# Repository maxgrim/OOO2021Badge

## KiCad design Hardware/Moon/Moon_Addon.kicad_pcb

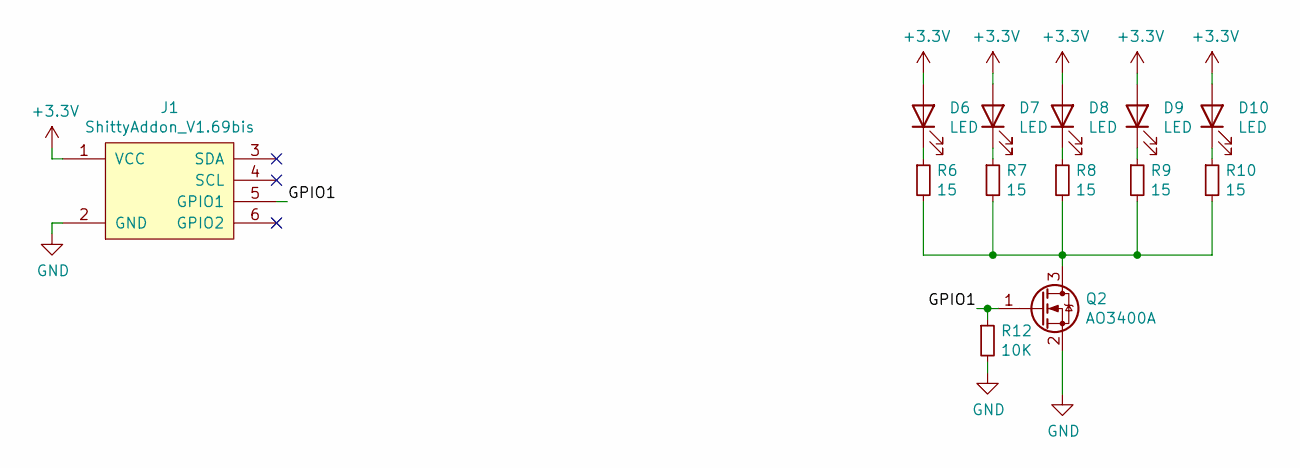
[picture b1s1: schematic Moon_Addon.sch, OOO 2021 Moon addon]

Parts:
D6, D7, D8, D9, D10: LED; LED_0805_2012Metric_Castellated; LCSC C34499
J1: ShittyAddon_V1.69bis; PinHeader_2x03_P2.54mm_Vertical
Q2: AO3400A; SOT-23; LCSC C20917
R6, R7, R8, R9, R10: 15; R_0805_2012Metric_Pad1.20x1.40mm_HandSolder; LCSC C17480
R12: 10K; R_0805_2012Metric_Pad1.20x1.40mm_HandSolder; LCSC C17414

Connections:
+3V3: D6.2 (A), D7.2 (A), D8.2 (A), D9.2 (A), D10.2 (A), J1.1 (VCC)
/GPIO1: J1.5 (GPIO1), Q2.1 (G), R12.1
GND: J1.2 (GND), Q2.2 (S), R12.2
unnamed: D6.1 (K), R6.1
unnamed: D7.1 (K), R7.1
unnamed: D8.1 (K), R8.1
unnamed: D9.1 (K), R9.1
unnamed: D10.1 (K), R10.1
unnamed: Q2.3 (D), R6.2, R7.2, R8.2, R9.2, R10.2

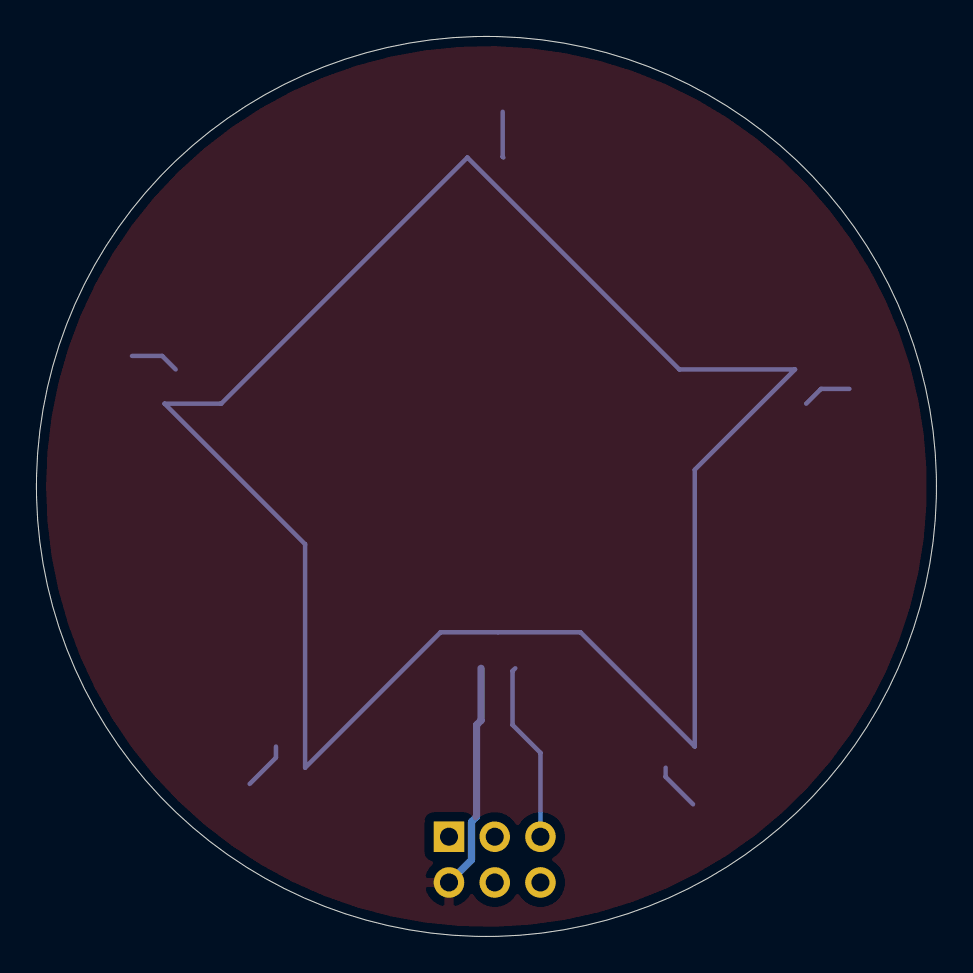
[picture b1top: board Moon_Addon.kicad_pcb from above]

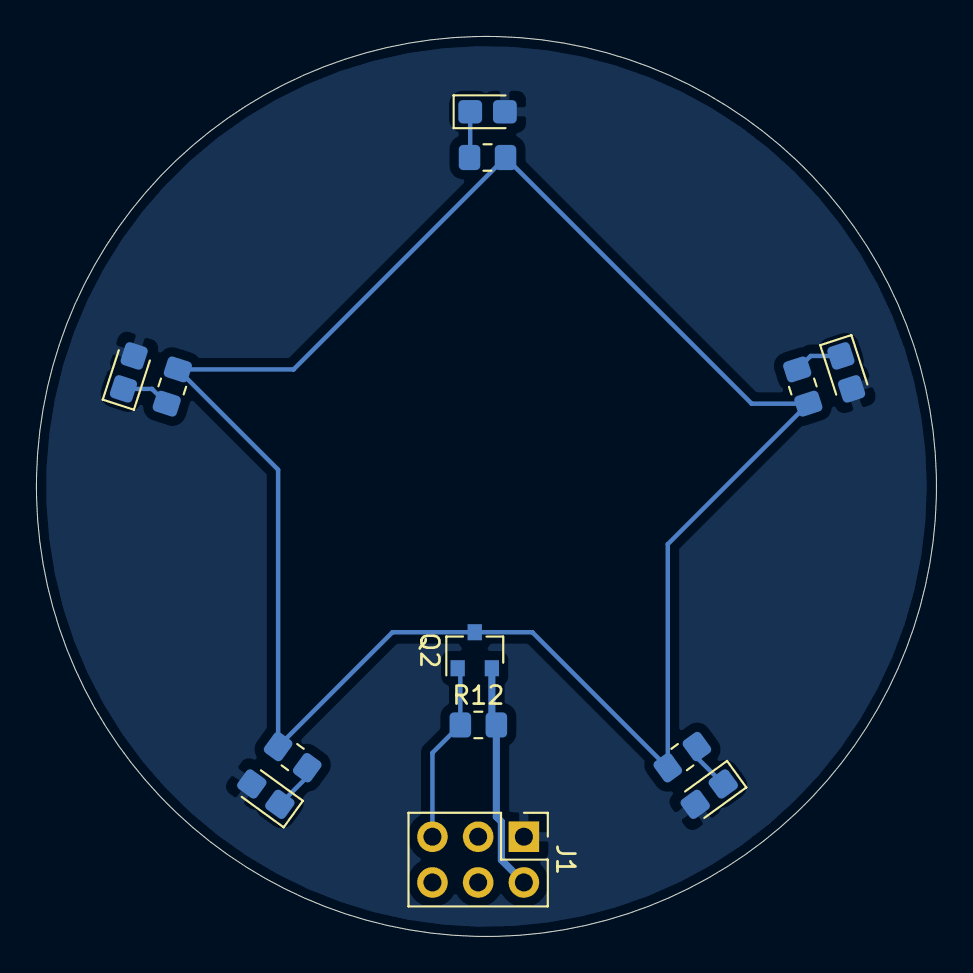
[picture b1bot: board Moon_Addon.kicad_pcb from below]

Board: 2 copper layers, 50.0 x 50.0 mm, 13 parts (13 on the bottom side), 9 nets.

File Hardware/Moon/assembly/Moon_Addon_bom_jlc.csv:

"Comment","Designator","Footprint","LCSC Part #"
"LED","D6,D7,D8,D9,D10","LED_0805_2012Metric_Castellated","C34499"
"AO3400A","Q2","SOT-23","C20917"
"15","R6,R7,R8,R9,R10","R_0805_2012Metric_Pad1.20x1.40mm_HandSolder","C17480"
"10K","R12","R_0805_2012Metric_Pad1.20x1.40mm_HandSolder","C17414"

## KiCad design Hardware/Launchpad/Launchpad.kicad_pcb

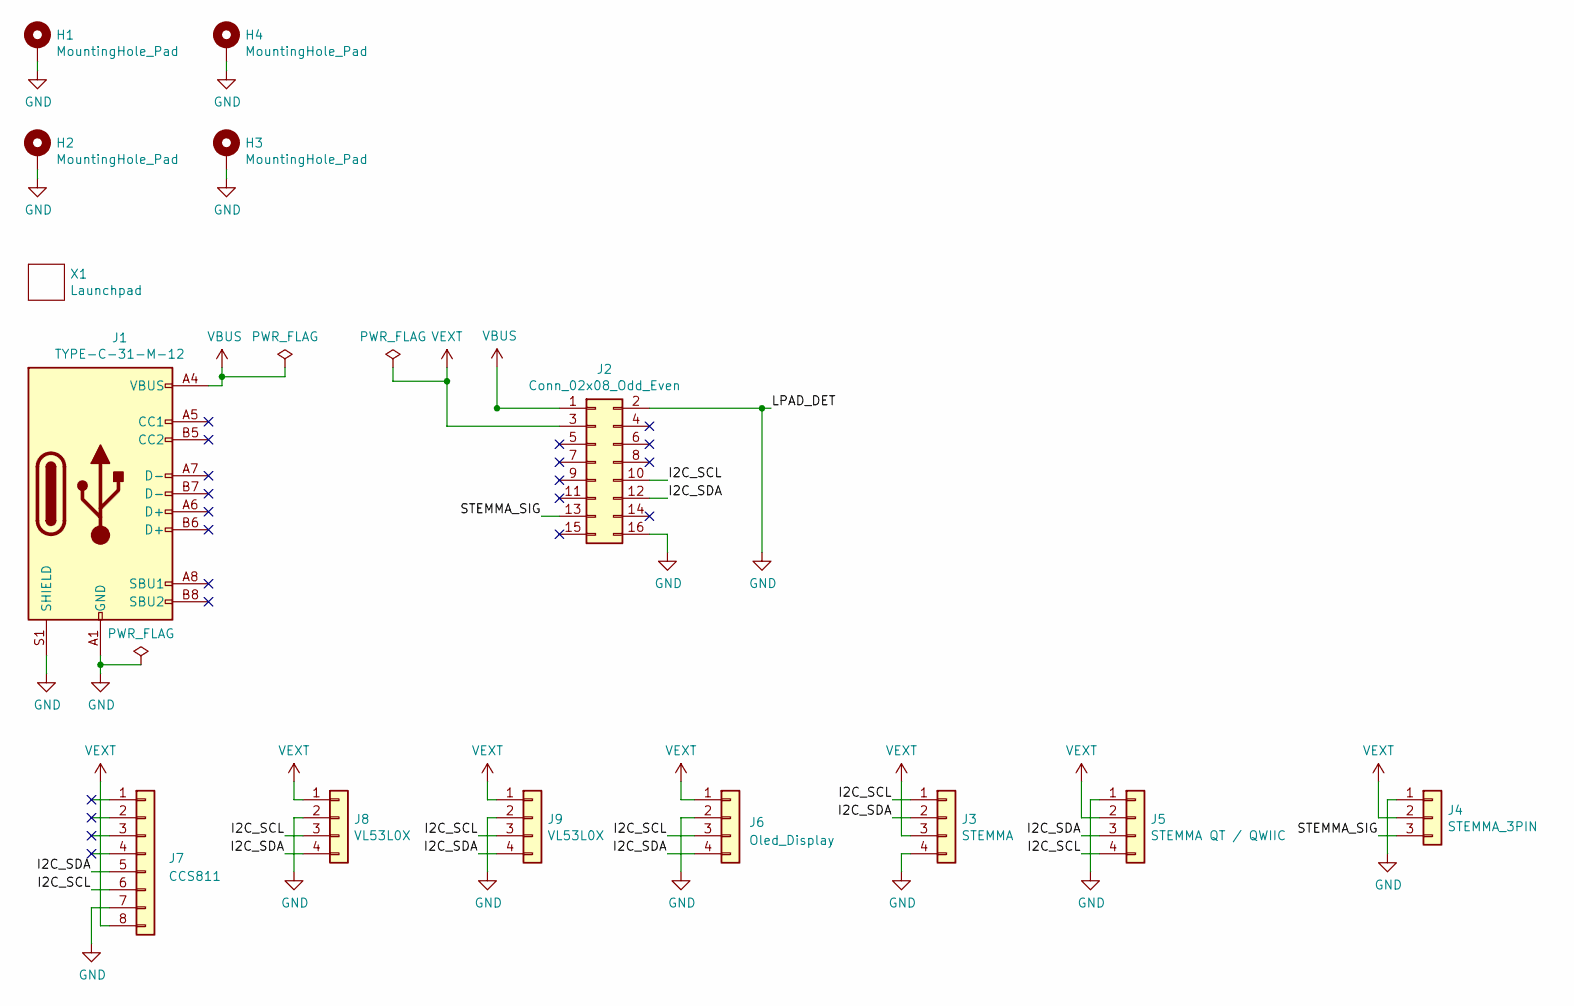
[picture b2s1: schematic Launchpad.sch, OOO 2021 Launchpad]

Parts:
H1, H2, H3, H4: MountingHole_Pad; MountingHole_4.3mm_M4_Pad_Via
J1: TYPE-C-31-M-12; LCSC C165948
J2: Conn_02x08_Odd_Even; PinHeader_2x08_P2.54mm_Horizontal; LCSC C492436
J3: STEMMA; CONN-SMD_2001SMT-4P-WT; LCSC C132498
J4: STEMMA_3PIN; CONN-SMD_3P-P2.00_2001SMT-3P_P; LCSC C155895
J5: STEMMA QT / QWIIC; CONN-SMD_1.0T-4P; LCSC C145956
J6: Oled_Display; PinSocket_1x04_P2.54mm_Horizontal; LCSC C225512
J7: CCS811; PinSocket_1x08_P2.54mm_Vertical; LCSC C350308
J8, J9: VL53L0X; PinSocket_1x04_P2.54mm_Vertical; LCSC C350310
X1: Launchpad

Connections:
/I2C_SCL: J2.10, J3.1, J5.4, J6.3, J7.6, J8.3, J9.3
/I2C_SDA: J2.12, J3.2, J5.3, J6.4, J7.5, J8.4, J9.4
/STEMMA_SIG: J2.13, J4.3
GND: H1.1, H2.1, H3.1, H4.1, J1.A1 (GND), J1.A12 (GND), J1.B1 (GND), J1.B12 (GND), J1.S1 (SHIELD), J2.2, J2.16, J3.4, J4.1, J5.1, J6.2, J7.7, J8.2, J9.2
VBUS: J1.A4 (VBUS), J1.A9 (VBUS), J1.B4 (VBUS), J1.B9 (VBUS), J2.1
VEXT: J2.3, J3.3, J4.2, J5.2, J6.1, J7.8, J8.1, J9.1

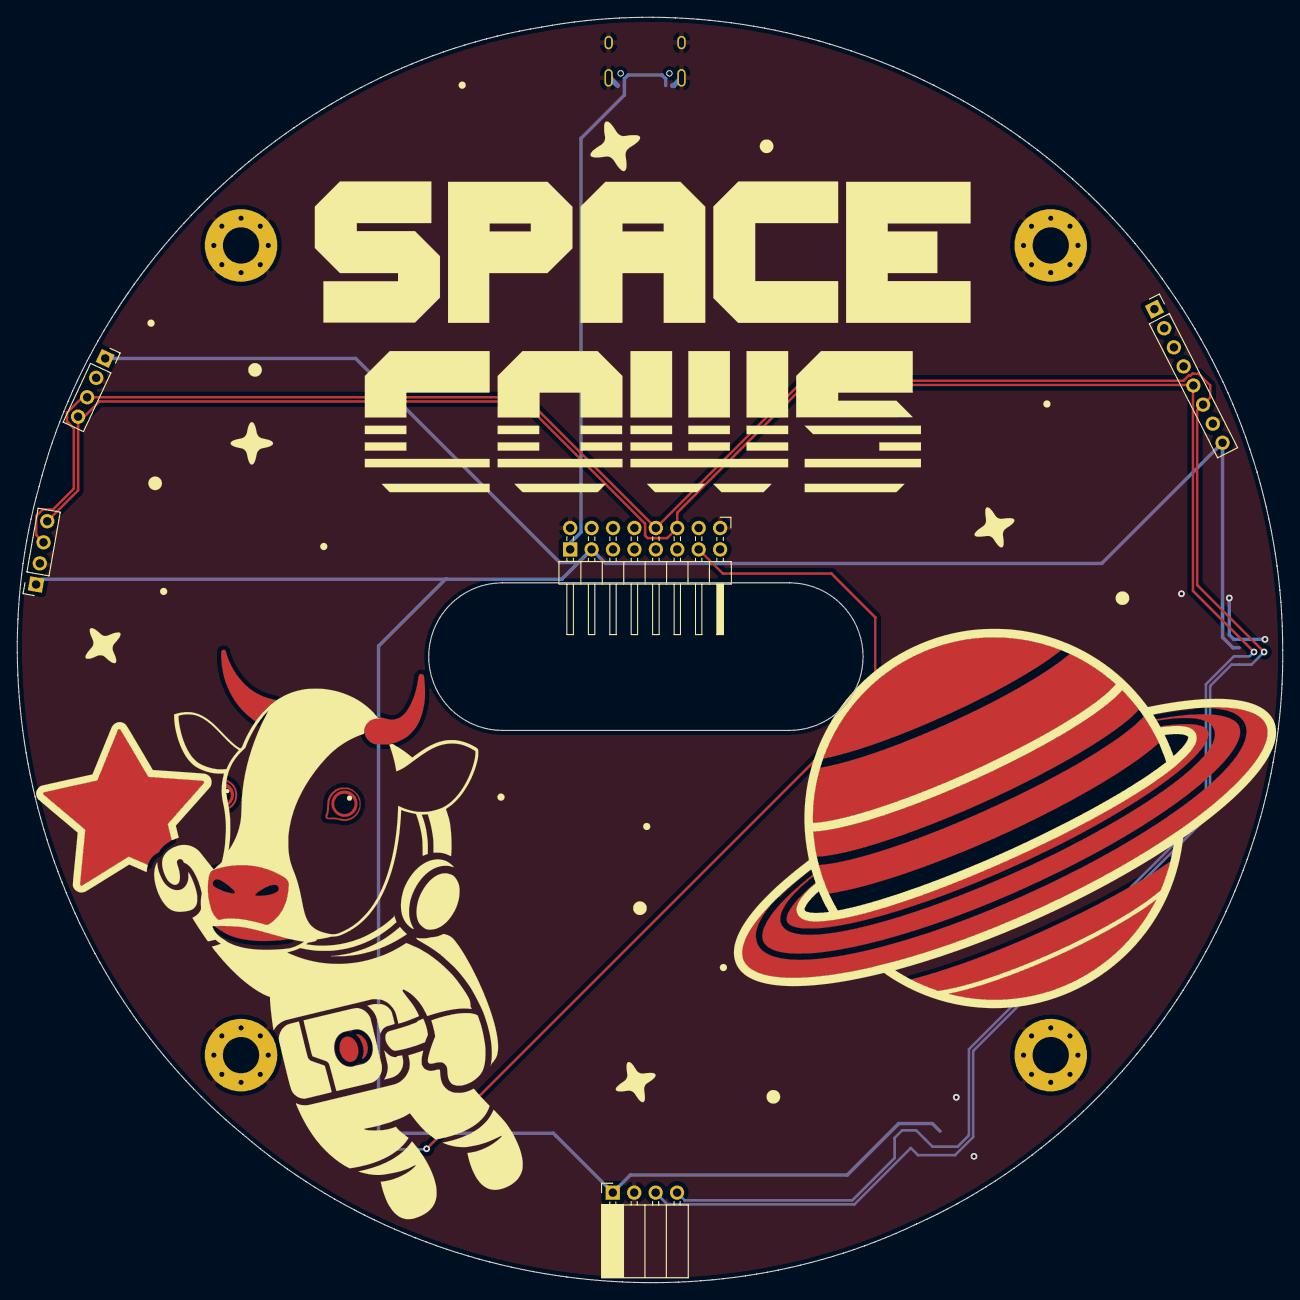
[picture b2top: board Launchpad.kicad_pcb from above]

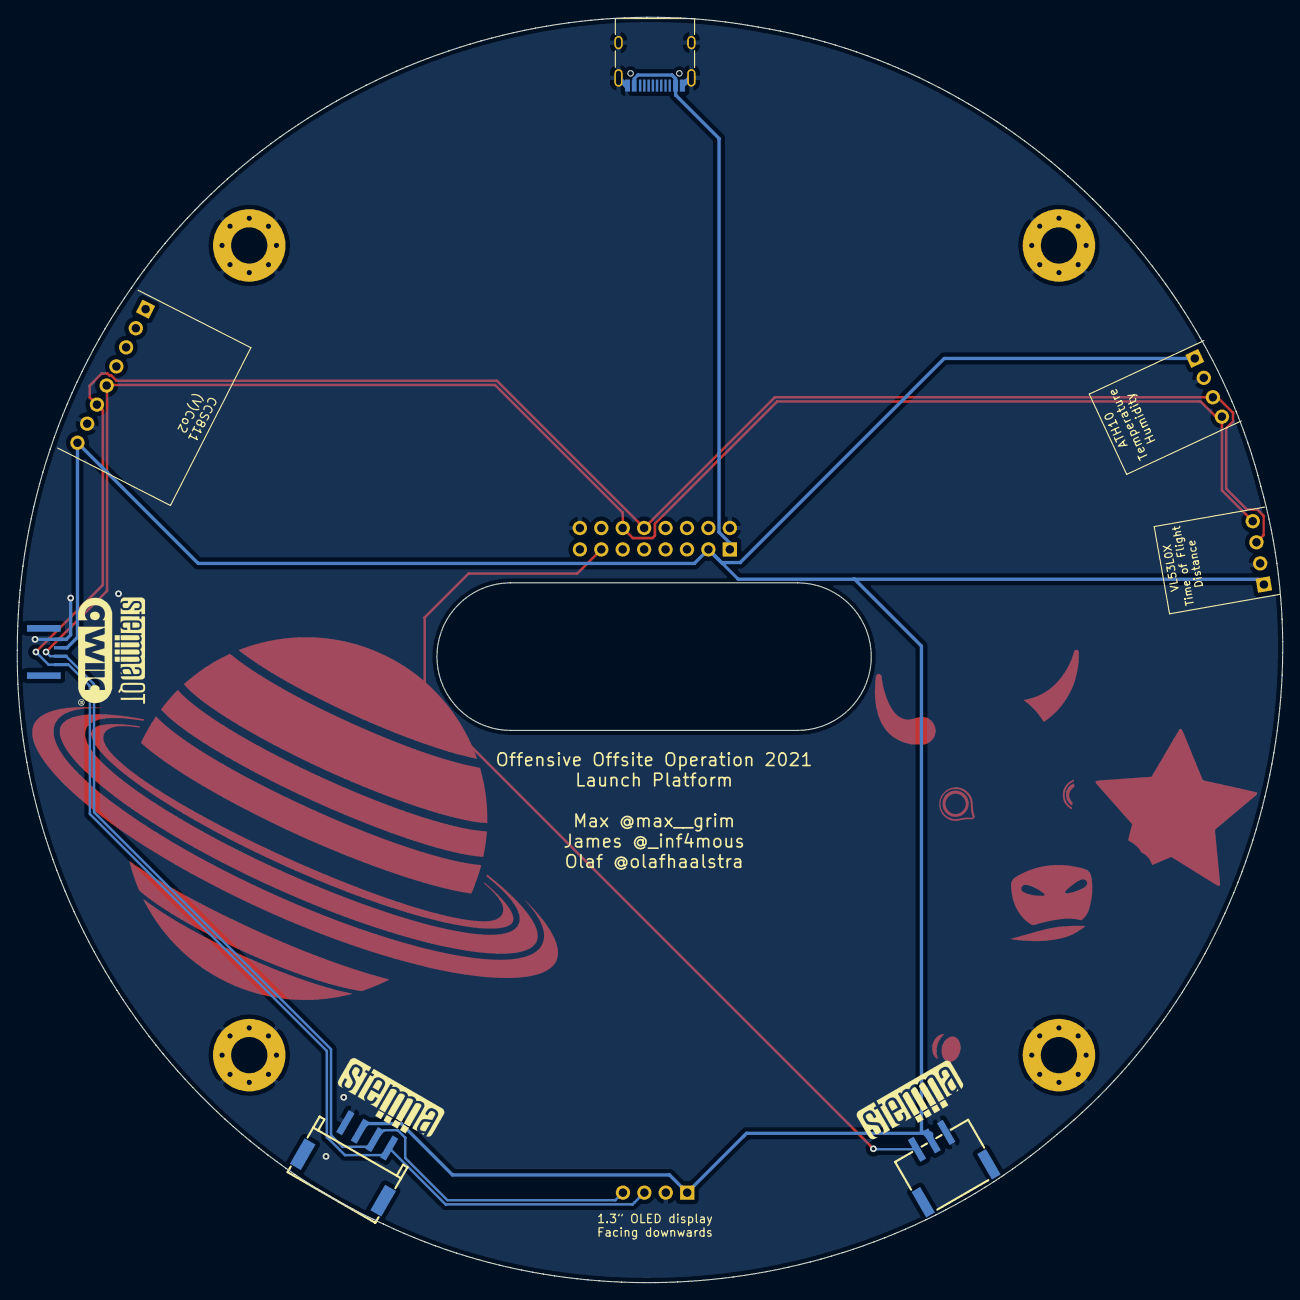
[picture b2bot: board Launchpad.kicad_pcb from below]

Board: 2 copper layers, 150.0 x 150.0 mm, 14 parts (4 on the bottom side), 6 nets.

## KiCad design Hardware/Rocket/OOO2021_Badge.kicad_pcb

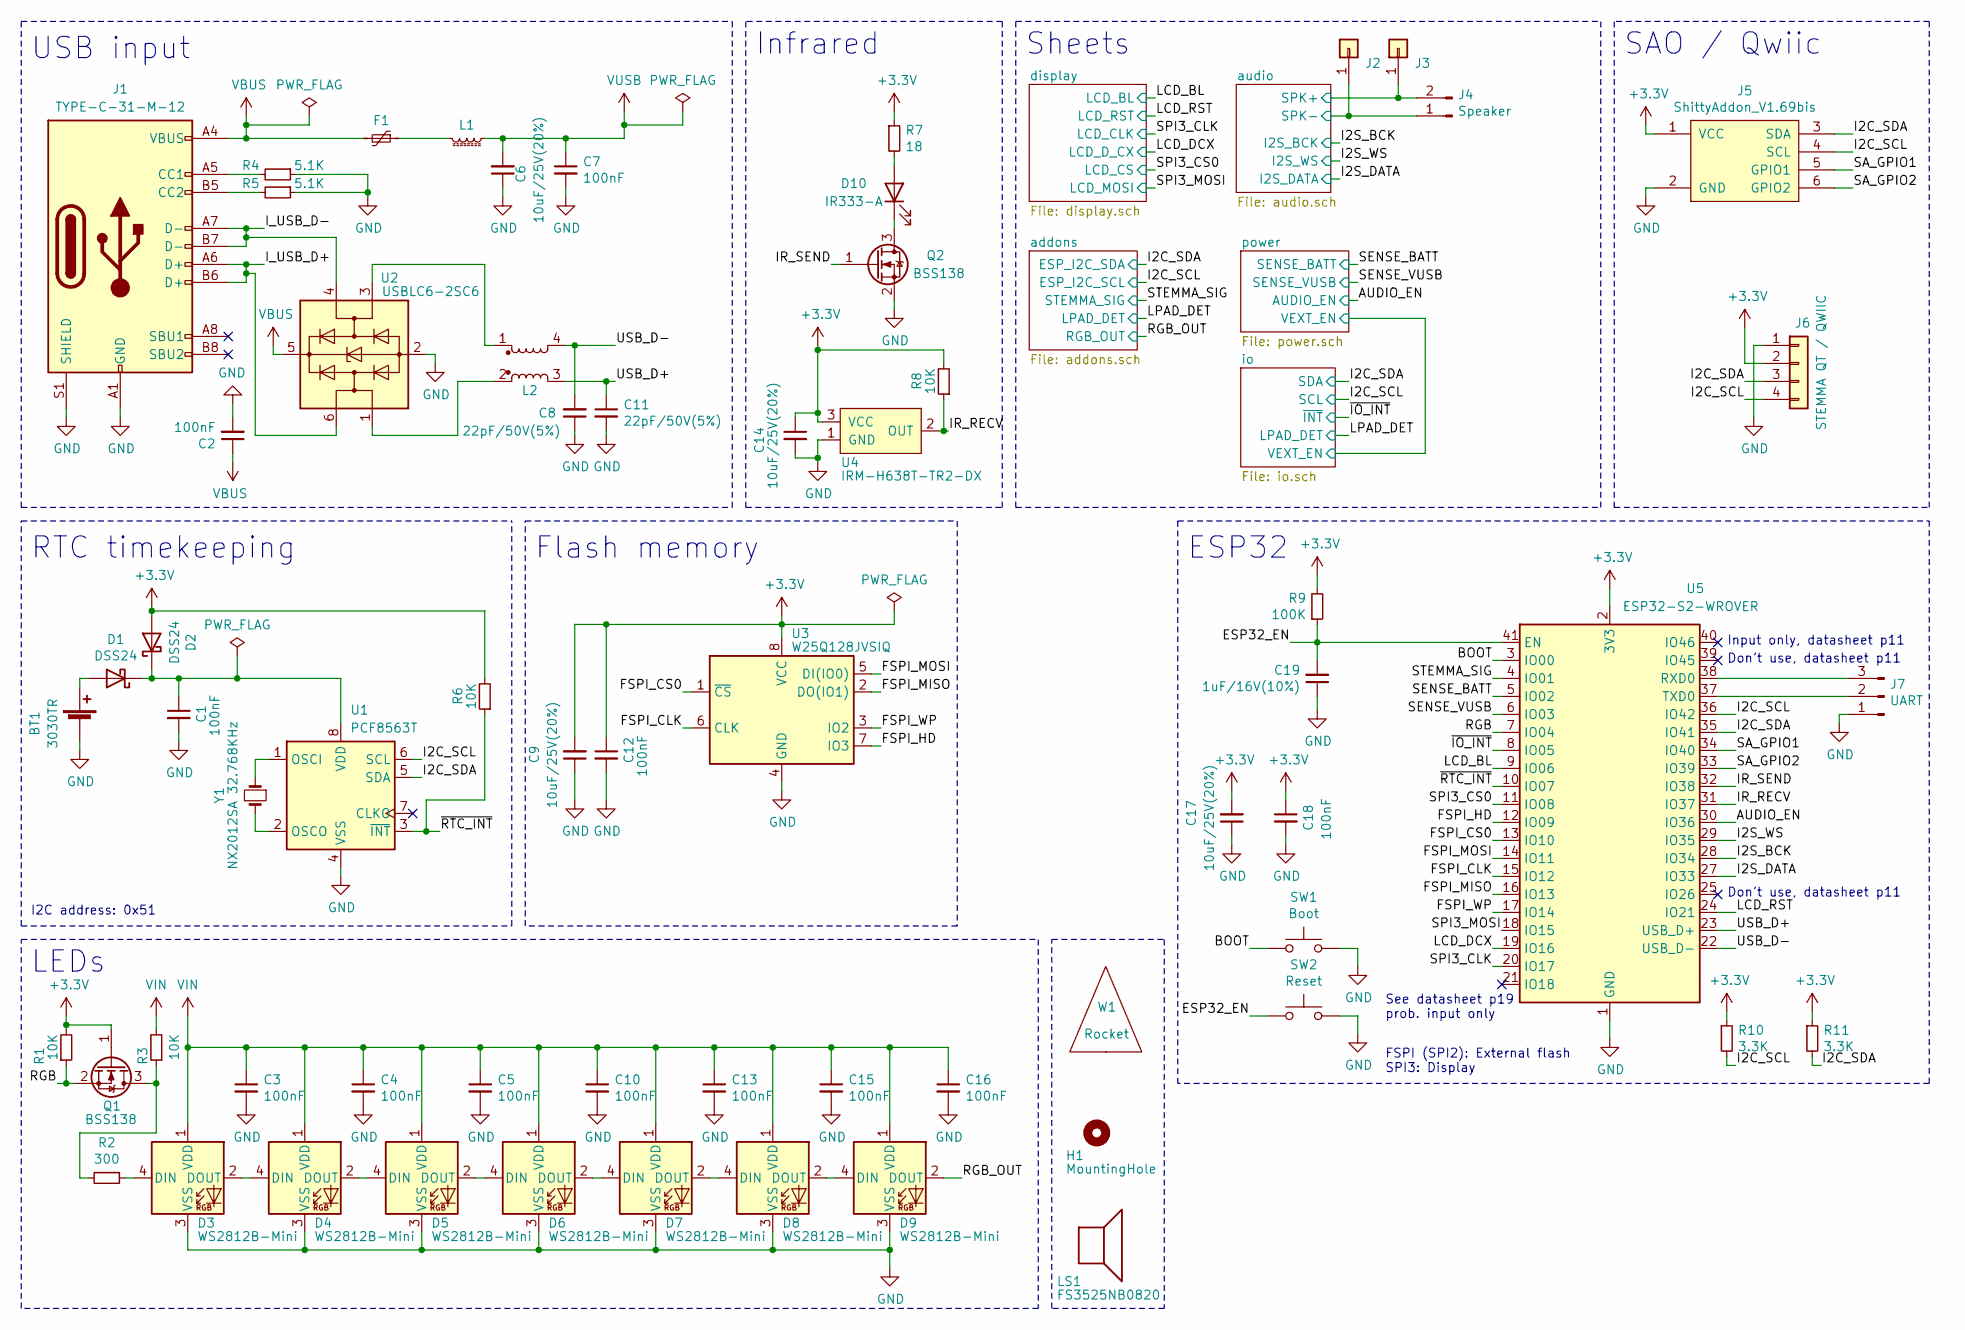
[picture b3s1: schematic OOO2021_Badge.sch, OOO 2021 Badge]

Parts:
BT1: 3030TR; 3030
C1, C2, C3, C4, C5, C7, C10, C12, C13, C15, C16, C18: 100nF; C_0402_1005Metric; LCSC C1581
C6, C9, C14, C17: 10uF/25V(20%); C_0603_1608Metric; LCSC C91606
C8, C11: 22pF/50V(5%); C_0402_1005Metric; LCSC C1555
C19: 1uF/16V(10%); C_0402_1005Metric; LCSC C29266
D1, D2: DSS24; D_SOD-123; LCSC C511865
D3, D4, D5, D6, D7, D8, D9: WS2812B-Mini; LED-SMD_4P-L3.5-W3.5-TL_WS2812B; LCSC C114583
D10: IR333-A; LED_D5.0mm; LCSC C264290
F1: JK-SMD0805-100; Fuse_0805_2012Metric_Castellated; LCSC C369152
H1: MountingHole; MountingHole_3mm
J1: TYPE-C-31-M-12; LCSC C165948
J2, J3: Conn_01x01; TestPoint_Pad_2.0x2.0mm
J4: Speaker; CONN-SMD_P1.25-H_1.25T-2PWT; LCSC C22074
J5: ShittyAddon_V1.69bis; PinSocket_2x03_P2.54mm_Vertical; LCSC C92272
J6: STEMMA QT / QWIIC; CONN-SMD_1.0T-4P; LCSC C145956
J7: UART; PinHeader_1x03_P2.54mm_Vertical_SMD_Pin1Left
L1: UPZ1608E221-2R2TF; L_0603_1608Metric; LCSC C96997
L2: ACM2012E-900-2P-T00; IND-SMD_4P-L2.0-W1.2-TL; LCSC C76573
LS1: FS3525NB0820; FS3525NB0820-H5.6; LCSC C782114
Q1, Q2: BSS138; SOT-23; LCSC C426569
R1, R3, R6, R8: 10K; R_0402_1005Metric; LCSC C25744
R2: 300; R_0402_1005Metric; LCSC C25102
R4, R5: 5.1K; R_0402_1005Metric; LCSC C25905
R7: 18; R_0603_1608Metric; LCSC C22830
R9: 100K; R_0402_1005Metric; LCSC C25530
R10, R11: 3.3K; R_0402_1005Metric; LCSC C25890
SW1: Boot; SW-SMD_4P-L5.1-W5.1-P3.70-LS6.5-TL-2; LCSC C318887
SW2: Reset; SW-SMD_4P-L5.1-W5.1-P3.70-LS6.5-TL-2; LCSC C318887
U1: PCF8563T; SOIC-8_3.9x4.9mm_P1.27mm; LCSC C7440
U2: USBLC6-2SC6; SOT-23-6; LCSC C558442
U3: W25Q128JVSIQ; SOIC-8_5.275x5.275mm_P1.27mm; LCSC C97521
U4: IRM-H638T-TR2-DX; LCSC C390031
U5: ESP32-S2-WROVER; LCSC C967027
W1: Rocket
Y1: NX2012SA 32.768KHz; Crystal_SMD_2012-2Pin_2.0x1.2mm; LCSC C528982

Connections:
+3V3: C9.2, C12.1, C14.1, C17.2, C18.1, D2.2 (A), J5.1 (VCC), J6.2, Q1.1 (G), R1.2, R6.2, R7.1, R8.2, R9.2, R10.1, R11.1, U3.8 (VCC), U4.3 (VCC), U5.2 (3V3); also elsewhere on the board
/AUDIO_EN: U5.30 (IO36); also elsewhere on the board
/BOOT: SW1.1, U5.3 (IO00)
/ESP32_EN: C19.2, R9.1, SW2.1, U5.41 (EN)
/FSPI_CLK: U3.6 (CLK), U5.15 (IO12)
/FSPI_CS0: U3.1 (~CS), U5.13 (IO10)
/FSPI_HD: U3.7 (IO3), U5.12 (IO09)
/FSPI_MISO: U3.2 (DO(IO1)), U5.16 (IO13)
/FSPI_MOSI: U3.5 (DI(IO0)), U5.14 (IO11)
/FSPI_WP: U3.3 (IO2), U5.17 (IO14)
/I2C_SCL: J5.4 (SCL), J6.4, R10.2, U1.6 (SCL), U5.36 (IO42); also elsewhere on the board
/I2C_SDA: J5.3 (SDA), J6.3, R11.2, U1.5 (SDA), U5.35 (IO41); also elsewhere on the board
/I2S_BCK: U5.28 (IO34); also elsewhere on the board
/I2S_DATA: U5.27 (IO33); also elsewhere on the board
/I2S_WS: U5.29 (IO35); also elsewhere on the board
/IR_RECV: R8.1, U4.2 (OUT), U5.31 (IO37)
/IR_SEND: Q2.1 (G), U5.32 (IO38)
/I_USB_D+: J1.A6 (D+), J1.B6 (D+), U2.6 (I/O1)
/I_USB_D-: J1.A7 (D-), J1.B7 (D-), U2.4 (I/O2)
/LCD_BL: U5.9 (IO06); also elsewhere on the board
/LCD_DCX: U5.19 (IO16); also elsewhere on the board
/LCD_RST: U5.24 (IO21); also elsewhere on the board
/RGB: Q1.2 (S), R1.1, U5.7 (IO04)
/RGB_OUT: D9.2 (DOUT); also elsewhere on the board
/SA_GPIO1: J5.5 (GPIO1), U5.34 (IO40)
/SA_GPIO2: J5.6 (GPIO2), U5.33 (IO39)
/SENSE_BATT: U5.5 (IO02); also elsewhere on the board
/SENSE_VUSB: U5.6 (IO03); also elsewhere on the board
/SPI3_CLK: U5.20 (IO17); also elsewhere on the board
/SPI3_CS0: U5.11 (IO08); also elsewhere on the board
/SPI3_MOSI: U5.18 (IO15); also elsewhere on the board
/STEMMA_SIG: U5.4 (IO01); also elsewhere on the board
/USB_D+: C11.1, L2.3, U5.23 (USB_D+)
/USB_D-: C8.2, L2.4, U5.22 (USB_D-)
/audio/SPK+: J3.1, J4.2; also elsewhere on the board
/audio/SPK-: J2.1, J4.1; also elsewhere on the board
/~IO_INT: U5.8 (IO05); also elsewhere on the board
/~RTC_INT: R6.1, U1.3 (~INT~), U5.10 (IO07)
GND: BT1.2 (-), C1.2, C2.2, C3.2, C4.2, C5.2, C6.1, C7.2, C8.1, C9.1, C10.2, C11.2, C12.2, C13.2, C14.2, C15.2, C16.2, C17.1, C18.2, C19.1, D3.3 (VSS), D4.3 (VSS), D5.3 (VSS), D6.3 (VSS), D7.3 (VSS), D8.3 (VSS), D9.3 (VSS), J1.A1 (GND), J1.A12 (GND), J1.B1 (GND), J1.B12 (GND), J1.S1 (SHIELD), J5.2 (GND), J6.1, J7.1, Q2.2 (S), R4.1, R5.1, SW1.2, SW2.2, U1.4 (VSS), U2.2 (GND), U3.4 (GND), U4.1 (GND), U5.1 (GND), U5.26 (GND), U5.42 (GND), U5.43 (GND); also elsewhere on the board
unnamed: BT1.1 (+), D1.2 (A)
unnamed: C1.1, D1.1 (K), D2.1 (K), U1.8 (VDD)
unnamed: D3.2 (DOUT), D4.4 (DIN)
unnamed: D3.4 (DIN), R2.1
unnamed: D4.2 (DOUT), D5.4 (DIN)
unnamed: D5.2 (DOUT), D6.4 (DIN)
unnamed: D6.2 (DOUT), D7.4 (DIN)
unnamed: D7.2 (DOUT), D8.4 (DIN)
unnamed: D8.2 (DOUT), D9.4 (DIN)
unnamed: D10.1 (K), Q2.3 (D)
unnamed: D10.2 (A), R7.2
unnamed: F1.1, L1.2
unnamed: J1.A5 (CC1), R4.2
unnamed: J1.B5 (CC2), R5.2
unnamed: J7.2, U5.37 (TXD0)
unnamed: J7.3, U5.38 (RXD0)
unnamed: L2.1, U2.3 (I/O2)
unnamed: L2.2, U2.1 (I/O1)
unnamed: Q1.3 (D), R2.2, R3.1
unnamed: U1.1 (OSCI), Y1.1
unnamed: U1.2 (OSCO), Y1.2
VBUS: C2.1, F1.2, J1.A4 (VBUS), J1.A9 (VBUS), J1.B4 (VBUS), J1.B9 (VBUS), U2.5 (VBUS); also elsewhere on the board
VIN: C3.1, C4.1, C5.1, C10.1, C13.1, C15.1, C16.1, D3.1 (VDD), D4.1 (VDD), D5.1 (VDD), D6.1 (VDD), D7.1 (VDD), D8.1 (VDD), D9.1 (VDD), R3.2; also elsewhere on the board
VUSB: C6.2, C7.1, L1.1; also elsewhere on the board

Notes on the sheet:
Don’t use, datasheet p11
See datasheet p19 prob. input only
Flash memory
USB input
ESP32
Sheets
LEDs
Infrared
Input only, datasheet p11
RTC timekeeping
FSPI (SPI2): External flash SPI3: Display
I2C address: 0x51
SAO / Qwiic

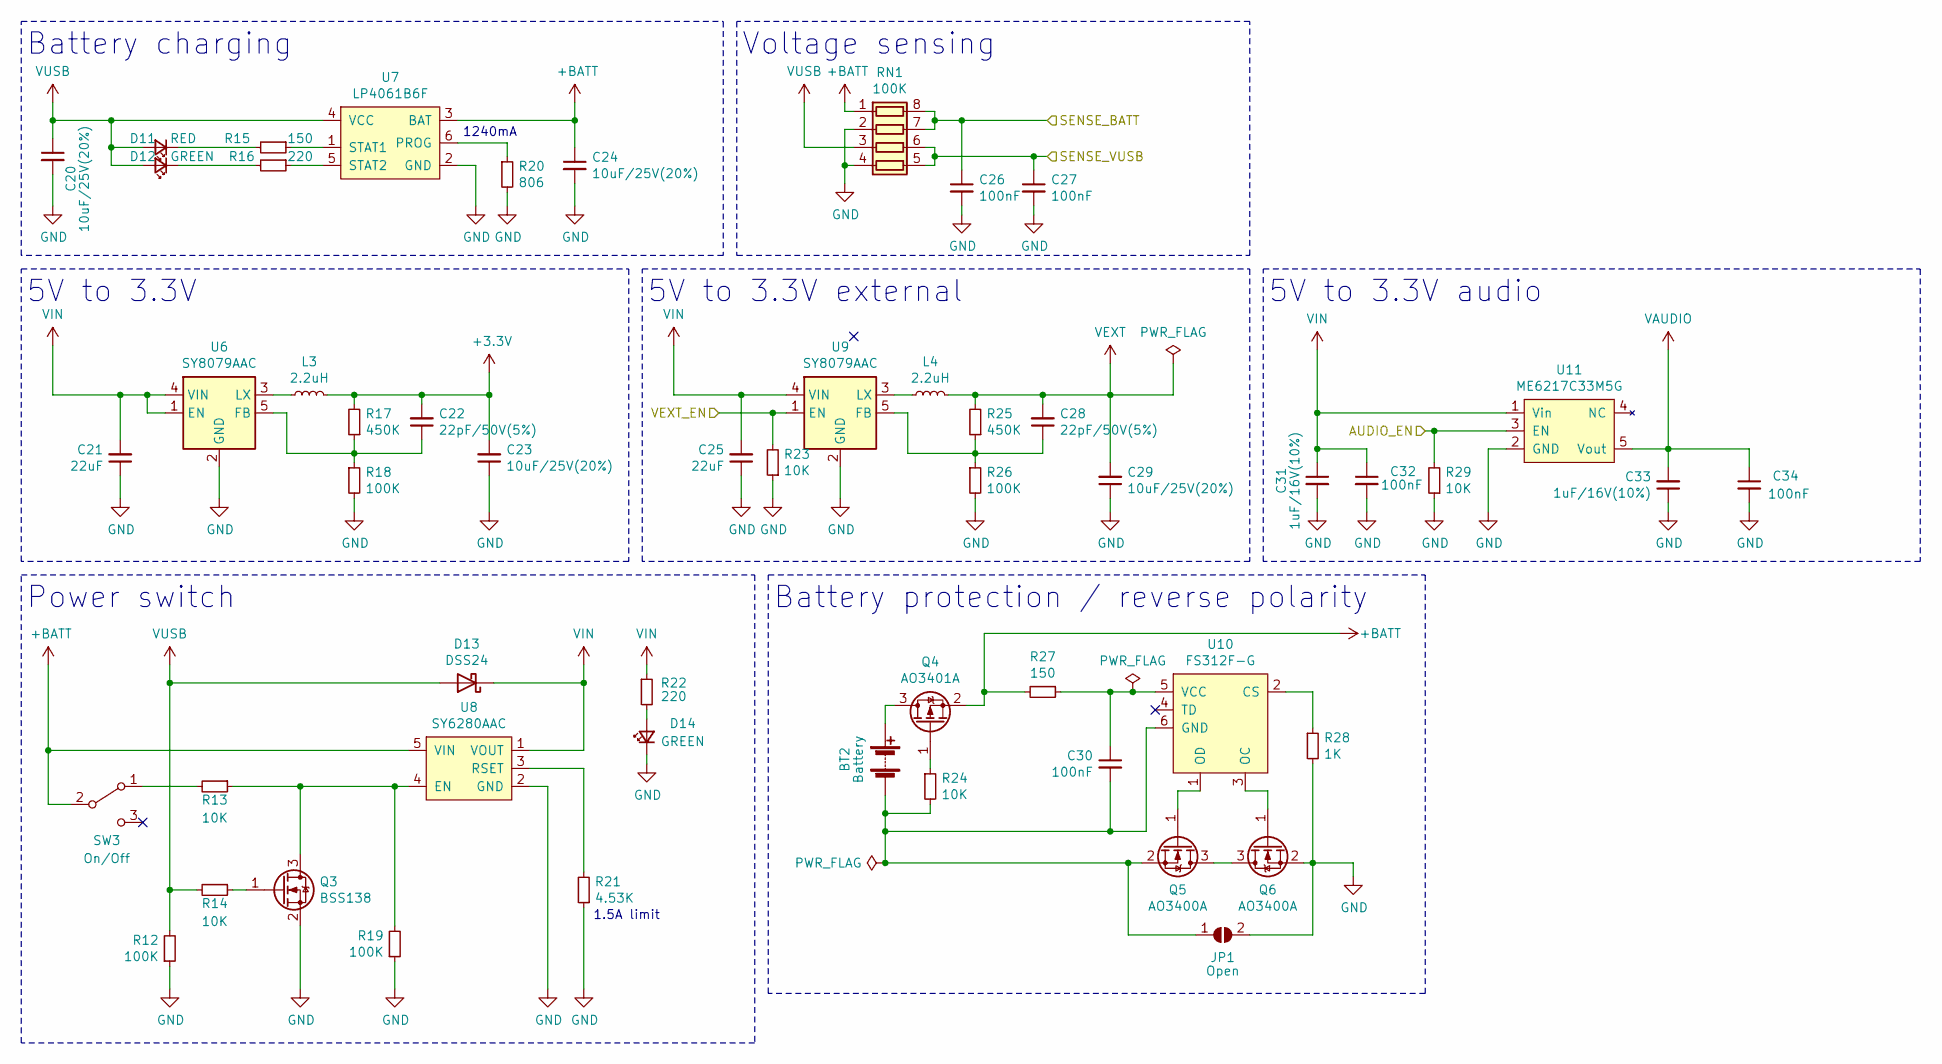
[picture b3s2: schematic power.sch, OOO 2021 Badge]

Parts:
BT2: Battery; BatteryHolder_Keystone_1042_1x18650
C20, C23, C24, C29: 10uF/25V(20%); C_0603_1608Metric; LCSC C91606
C21, C25: 22uF; C_0805_2012Metric; LCSC C45783
C22, C28: 22pF/50V(5%); C_0402_1005Metric; LCSC C1555
C26, C27, C30, C32, C34: 100nF; C_0402_1005Metric; LCSC C1581
C31, C33: 1uF/16V(10%); C_0402_1005Metric; LCSC C29266
D11: RED; LED_0603_1608Metric_Castellated; LCSC C84263
D12, D14: GREEN; LED_0603_1608Metric_Castellated; LCSC C205443
D13: DSS24; D_SOD-123; LCSC C511865
JP1: Open; SolderJumper-2_P1.3mm_Open_RoundedPad1.0x1.5mm
L3, L4: 2.2uH; L0806; LCSC C136243
Q3: BSS138; SOT-23; LCSC C426569
Q4: AO3401A; SOT-23; LCSC C15127
Q5, Q6: AO3400A; SOT-23; LCSC C344010
R12, R18, R19, R26: 100K; R_0402_1005Metric; LCSC C25530
R13, R14, R23, R24, R29: 10K; R_0402_1005Metric; LCSC C25744
R15, R27: 150; R_0402_1005Metric; LCSC C25082
R16, R22: 220; R_0402_1005Metric; LCSC C25091
R17, R25: 450K; R_0402_1005Metric; LCSC C407681
R20: 806; R_0402_1005Metric; LCSC C407662
R21: 4.53K; R_0402_1005Metric; LCSC C79537
R28: 1K; R_0402_1005Metric; LCSC C11702
RN1: 100K; R_Array_Convex_4x0603; LCSC C173315
SW3: On/Off; SW-TH_MSK12C02-HB; LCSC C431541
U6, U9: SY8079AAC; SOT-23-5; LCSC C133751
U7: LP4061B6F; SOT-23-6; LCSC C517027
U8: SY6280AAC; SOT-23-5; LCSC C55136
U10: FS312F-G; SOT-23-6; LCSC C82736
U11: ME6217C33M5G; SOT-23-5; LCSC C427602

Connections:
+3V3: C22.2, C23.2, L3.2, R17.2; also elsewhere on the board
+BATT: C24.1, Q4.2 (S), R27.2, RN1.1 (R1.1), SW3.2 (B), U7.3 (BAT), U8.5 (VIN)
/AUDIO_EN: R29.2, U11.3 (EN); also elsewhere on the board
/SENSE_BATT: C26.1, RN1.7 (R2.2), RN1.8 (R1.2); also elsewhere on the board
/SENSE_VUSB: C27.1, RN1.5 (R4.2), RN1.6 (R3.2); also elsewhere on the board
/io/VEXT_EN: R23.2, U9.1 (EN); also elsewhere on the board
GND: C20.2, C21.1, C23.1, C24.2, C25.1, C26.2, C27.2, C29.1, C31.2, C32.2, C33.1, C34.2, D14.1 (K), JP1.2 (B), Q3.2 (S), Q6.2 (S), R12.1, R18.2, R19.1, R20.2, R21.1, R23.1, R26.2, R28.2, R29.1, RN1.2 (R2.1), RN1.4 (R4.1), U6.2 (GND), U7.2 (GND), U8.2 (GND), U9.2 (GND), U11.2 (GND); also elsewhere on the board
unnamed: BT2.1 (+), Q4.3 (D)
unnamed: BT2.2 (-), C30.2, JP1.1 (A), Q5.2 (S), R24.2, U10.6 (GND)
unnamed: C22.1, R17.1, R18.1, U6.5 (FB)
unnamed: C28.1, R25.1, R26.1, U9.5 (FB)
unnamed: C30.1, R27.1, U10.5 (VCC)
unnamed: D11.1 (K), R15.2
unnamed: D12.1 (K), R16.2
unnamed: D14.2 (A), R22.2
unnamed: L3.1, U6.3 (LX)
unnamed: L4.1, U9.3 (LX)
unnamed: Q3.1 (G), R14.1
unnamed: Q3.3 (D), R13.1, R19.2, U8.4 (EN)
unnamed: Q4.1 (G), R24.1
unnamed: Q5.1 (G), U10.1 (OD)
unnamed: Q5.3 (D), Q6.3 (D)
unnamed: Q6.1 (G), U10.3 (OC)
unnamed: R13.2, SW3.1 (A)
unnamed: R15.1, U7.1 (STAT1)
unnamed: R16.1, U7.5 (STAT2)
unnamed: R20.1, U7.6 (PROG)
unnamed: R21.2, U8.3 (RSET)
unnamed: R28.1, U10.2 (CS)
VAUDIO: C33.2, C34.1, U11.5 (Vout); also elsewhere on the board
VEXT: C28.2, C29.2, L4.2, R25.2; also elsewhere on the board
VIN: C21.2, C25.2, C31.1, C32.1, D13.1 (K), R22.1, U6.1 (EN), U6.4 (VIN), U8.1 (VOUT), U9.4 (VIN), U11.1 (Vin); also elsewhere on the board
VUSB: C20.1, D11.2 (A), D12.2 (A), D13.2 (A), R12.2, R14.2, RN1.3 (R3.1), U7.4 (VCC); also elsewhere on the board

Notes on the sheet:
Battery charging
Power switch
5V to 3.3V
Battery protection / reverse polarity
Voltage sensing
5V to 3.3V external
5V to 3.3V audio
1.5A limit
1240mA

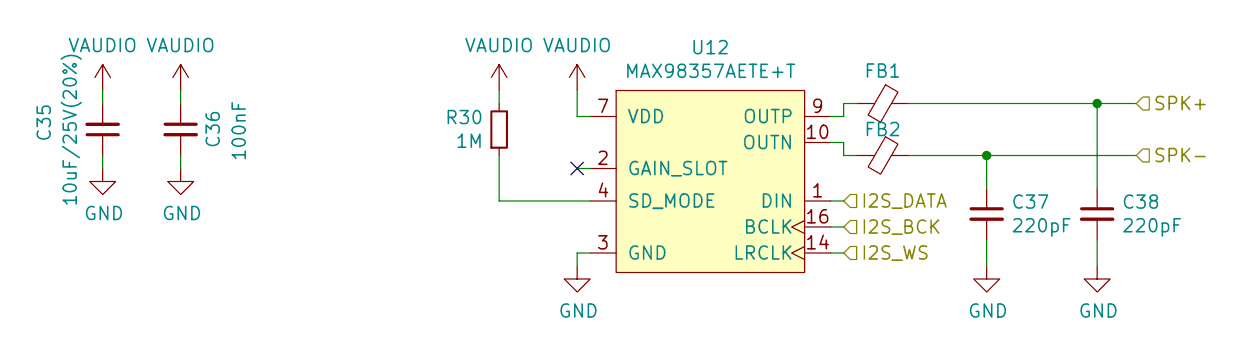
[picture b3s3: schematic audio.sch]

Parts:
C35: 10uF/25V(20%); C_0603_1608Metric; LCSC C91606
C36: 100nF; C_0402_1005Metric; LCSC C1581
C37, C38: 220pF; C_0402_1005Metric; LCSC C466236
FB1, FB2: PBY160808T-102Y-N; L_0603_1608Metric; LCSC C142079
R30: 1M; R_0402_1005Metric; LCSC C26083
U12: MAX98357AETE+T; QFN50P300X300X80-17N; LCSC C910544

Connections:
/I2S_BCK: U12.16 (BCLK); also elsewhere on the board
/I2S_DATA: U12.1 (DIN); also elsewhere on the board
/I2S_WS: U12.14 (LRCLK); also elsewhere on the board
/audio/SPK+: C38.1, FB1.1; also elsewhere on the board
/audio/SPK-: C37.1, FB2.1; also elsewhere on the board
GND: C35.1, C36.2, C37.2, C38.2, U12.3 (GND); also elsewhere on the board
unnamed: FB1.2, U12.9 (OUTP)
unnamed: FB2.2, U12.10 (OUTN)
unnamed: R30.1, U12.4 (SD_MODE)
VAUDIO: C35.2, C36.1, R30.2, U12.7 (VDD); also elsewhere on the board

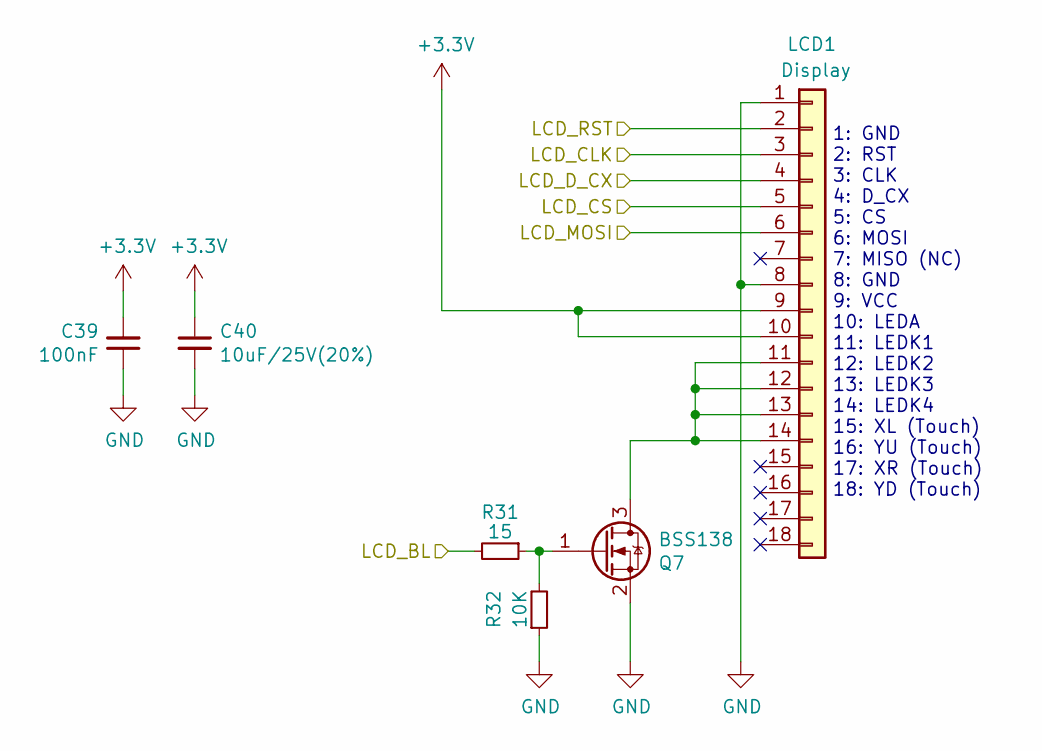
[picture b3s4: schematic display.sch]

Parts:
C39: 100nF; C_0402_1005Metric; LCSC C1581
C40: 10uF/25V(20%); C_0603_1608Metric; LCSC C91606
LCD1: Display; ILI9341_2.4
Q7: BSS138; SOT-23; LCSC C426569
R31: 15; R_0402_1005Metric; LCSC C208806
R32: 10K; R_0402_1005Metric; LCSC C25744

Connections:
+3V3: C39.2, C40.1, LCD1.9, LCD1.10; also elsewhere on the board
/LCD_BL: R31.2; also elsewhere on the board
/LCD_DCX: LCD1.4; also elsewhere on the board
/LCD_RST: LCD1.2; also elsewhere on the board
/SPI3_CLK: LCD1.3; also elsewhere on the board
/SPI3_CS0: LCD1.5; also elsewhere on the board
/SPI3_MOSI: LCD1.6; also elsewhere on the board
GND: C39.1, C40.2, LCD1.1, LCD1.8, Q7.2 (S), R32.1; also elsewhere on the board
unnamed: LCD1.11, LCD1.12, LCD1.13, LCD1.14, Q7.3 (D)
unnamed: Q7.1 (G), R31.1, R32.2

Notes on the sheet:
1: GND 2: RST 3: CLK 4: D_CX 5: CS 6: MOSI 7: MISO (NC) 8: GND 9: VCC 10: LEDA 11: LEDK1 12: LEDK2 13: LEDK3 14: LEDK4 15: XL (Touch) 16: YU (Touch) 17: XR (Touch) 18: YD (Touch)
